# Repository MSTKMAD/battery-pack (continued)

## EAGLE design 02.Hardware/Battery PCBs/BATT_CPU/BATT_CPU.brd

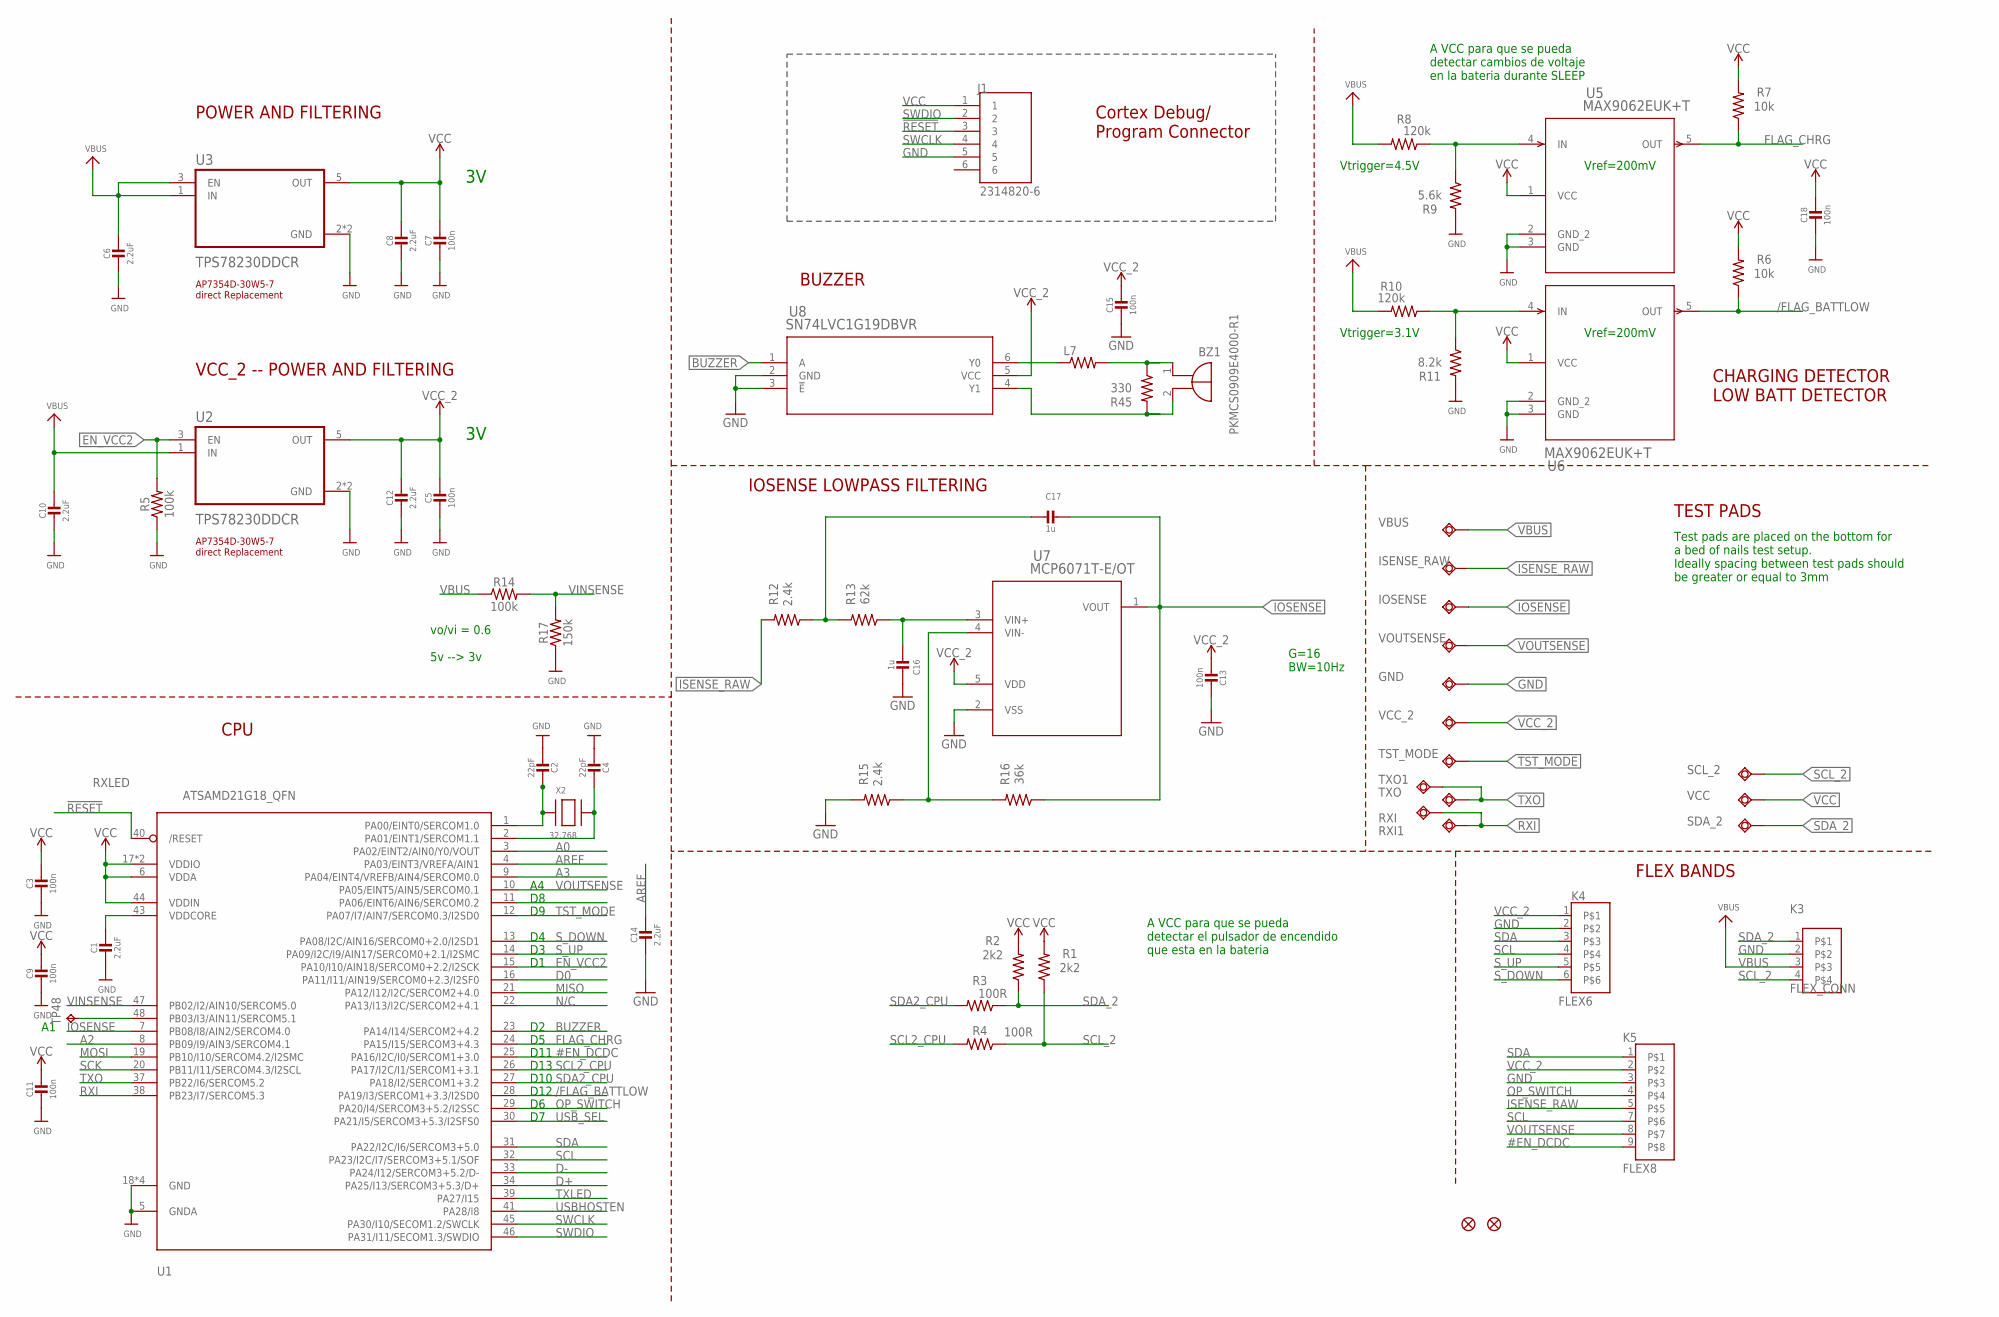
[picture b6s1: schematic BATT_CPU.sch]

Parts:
BZ1: PKMCS0909E4000-R1; PKMCS0909
C1, C14: 2.2uF; 0603-NO
C2, C4: 22pF; 0603-NO
C3, C5, C7, C9, C11, C13, C15, C18: 100n; 0603-NO
C6, C8, C10, C12: 2.2uF; 0805-NO
C16, C17: 1u; 0603-NO
GND: TESTPAD_TPSQB1,27; TESTPAD_B1,27
IOSENSE: TESTPAD_TPSQB1,27; TESTPAD_B1,27
ISENSE_RAW: TESTPAD_TPSQB1,27; TESTPAD_B1,27
J1: 2314820-6; TE_2314820-6
K3: FLEX_CONN; FLEX4
K4: FLEX6
K5: FLEX8
L7: MMZ2012Y202BT000; 0805
R1, R2: 2k2; 0603
R3, R4: 100R; 0603
R5, R14: 100k; 0603
R6, R7: 10k; 0603
R8, R10: 120k; 0603
R9: 5.6k; 0603
R11: 8.2k; 0603
R12, R15: 2.4k; 0603
R13: 62k; 0603
R16: 36k; 0603
R17: 150k; 0603
R45: 330; 0603
RXI, RXI1: TESTPAD_TPSQB1,27; TESTPAD_B1,27
SCL_2: TESTPAD_TPSQB1,27; TESTPAD_B1,27
SDA_2: TESTPAD_TPSQB1,27; TESTPAD_B1,27
TP48: TPTP08R; TP08R
TST_MODE: TESTPAD_TPSQB1,27; TESTPAD_B1,27
TXO, TXO1: TESTPAD_TPSQB1,27; TESTPAD_B1,27
U1: ATSAMD21G18_QFN; TQFN48_7MM
U2, U3: TPS78230DDCR; SOT95P280X110-5N
U5, U6: MAX9062EUK+T; 21-0057F_MXM
U7: MCP6071T-E/OT; SOT-23-5_MC_MCH
U8: SN74LVC1G19DBVR; DBV6
U$34, U$35: FIDUCIAL""; FIDUCIAL_1MM
VBUS: TESTPAD_TPSQB1,27; TESTPAD_B1,27
VCC: TESTPAD_TPSQB1,27; TESTPAD_B1,27
VCC_2: TESTPAD_TPSQB1,27; TESTPAD_B1,27
VOUTSENSE: TESTPAD_TPSQB1,27; TESTPAD_B1,27
X2: 32.768; XTAL3215

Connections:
!RESET: J1.3, U1.40 (/RESET)
#EN_DCDC: K5.9, U1.25 (PA16/I2C/I0/SERCOM1+3.0)
/FLAG_BATTLOW: R6.1, U1.28 (PA19/I3/SERCOM1+3.3/I2SD0), U6.5 (OUT)
A0: U1.3 (PA02/EINT2/AIN0/Y0/VOUT)
A2: U1.8 (PB09/I9/AIN3/SERCOM4.1)
A3: U1.9 (PA04/EINT4/VREFB/AIN4/SERCOM0.0)
AREF: C14.1, U1.4 (PA03/EINT3/VREFA/AIN1)
BUZZER: U1.23 (PA14/I14/SERCOM2+4.2), U8.1 (A)
D0: U1.16 (PA11/I11/AIN19/SERCOM0+2.3/I2SF0)
D+: U1.34 (PA25/I13/SERCOM3+5.3/D+)
D-: U1.33 (PA24/I12/SERCOM3+5.2/D-)
EN_VCC2: R5.2, U1.15 (PA10/I10/AIN18/SERCOM0+2.2/I2SCK), U2.3 (EN)
FLAG_CHRG: R7.1, U1.24 (PA15/I15/SERCOM3+4.3), U5.5 (OUT)
GND: C1.2, C2.2, C3.2, C4.2, C5.2, C6.2, C7.2, C8.2, C9.2, C10.2, C11.2, C12.2, C13.2, C14.2, C15.2, C16.2, C18.2, GND.TP, J1.5, K3.2, K4.2, K5.3, R5.1, R9.2, R11.2, R15.2, R17.1, U1.5 (GNDA), U1.18 (GND), U1.35 (GND), U1.42 (GND), U1.THERMAL (GND), U2.2 (GND), U2.4 (GND), U3.2 (GND), U3.4 (GND), U5.2 (GND_2), U5.3 (GND), U6.2 (GND_2), U6.3 (GND), U7.2 (VSS), U8.2 (GND), U8.3 (!E)
IOSENSE: C17.2, IOSENSE.TP, R16.1, U1.7 (PB08/I8/AIN2/SERCOM4.0), U7.1 (VOUT)
ISENSE_RAW: ISENSE_RAW.TP, K5.5, R12.2
MISO: U1.21 (PA12/I12/I2C/SERCOM2+4.0)
MOSI: U1.19 (PB10/I10/SERCOM4.2/I2SMC)
unnamed: R15.1, R16.2, U7.4 (VIN-)
unnamed: C2.1, U1.1 (PA00/EINT0/SERCOM1.0), X2.P$1
unnamed: C4.1, U1.2 (PA01/EINT1/SERCOM1.1), X2.P$2
unnamed: C17.1, R12.1, R13.2
unnamed: R10.1, R11.1, U6.4 (IN)
unnamed: R8.1, R9.1, U5.4 (IN)
unnamed: C16.1, R13.1, U7.3 (VIN+)
unnamed: TP48.TP, U1.48 (PB03/I3/AIN11/SERCOM5.1)
unnamed: L7.1, U8.6 (Y0)
unnamed: BZ1.1 (+), L7.2, R45.1
unnamed: BZ1.2 (-), R45.2, U8.4 (Y1)
OP_SWITCH: K5.4, U1.29 (PA20/I4/SERCOM3+5.2/I2SSC)
RXI: RXI.TP, RXI1.TP, U1.38 (PB23/I7/SERCOM5.3)
SCK: U1.20 (PB11/I11/SERCOM4.3/I2SCL)
SCL: K4.4, K5.7, U1.32 (PA23/I2C/I7/SERCOM3+5.1/SOF)
SCL2_CPU: R4.2, U1.26 (PA17/I2C/I1/SERCOM1+3.1)
SCL_2: K3.4, R1.1, R4.1, SCL_2.TP
SDA: K4.3, K5.1, U1.31 (PA22/I2C/I6/SERCOM3+5.0)
SDA2_CPU: R3.2, U1.27 (PA18/I2/SERCOM1+3.2)
SDA_2: K3.1, R2.1, R3.1, SDA_2.TP
SWCLK: J1.4, U1.45 (PA30/I10/SECOM1.2/SWCLK)
SWDIO: J1.2, U1.46 (PA31/I11/SECOM1.3/SWDIO)
S_DOWN: K4.6, U1.13 (PA08/I2C/AIN16/SERCOM0+2.0/I2SD1)
S_UP: K4.5, U1.14 (PA09/I2C/I9/AIN17/SERCOM0+2.1/I2SMC)
TST_MODE: TST_MODE.TP, U1.12 (PA07/I7/AIN7/SERCOM0.3/I2SD0)
TXO: TXO.TP, TXO1.TP, U1.37 (PB22/I6/SERCOM5.2)
USB_SEL: U1.30 (PA21/I5/SERCOM3+5.3/I2SFS0)
VBUS: C6.1, C10.1, K3.3, R8.2, R10.2, R14.1, U2.1 (IN), U3.1 (IN), U3.3 (EN), VBUS.TP
VCC: C3.1, C7.1, C8.1, C9.1, C11.1, C18.1, J1.1, R1.2, R2.2, R6.2, R7.2, U1.6 (VDDA), U1.17 (VDDIO), U1.36 (VDDIO), U1.44 (VDDIN), U3.5 (OUT), U5.1 (VCC), U6.1 (VCC), VCC.TP
VCC_2: C5.1, C12.1, C13.1, C15.1, K4.1, K5.2, U2.5 (OUT), U7.5 (VDD), U8.5 (VCC), VCC_2.TP
VDDCORE: C1.1, U1.43 (VDDCORE)
VINSENSE: R14.2, R17.2, U1.47 (PB02/I2/AIN10/SERCOM5.0)
VOUTSENSE: K5.8, U1.10 (PA05/EINT5/AIN5/SERCOM0.1), VOUTSENSE.TP

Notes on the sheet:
POWER AND FILTERING
N/C
TXLED
USBHOSTEN
RXLED
Cortex Debug/ Program Connector
BUZZER
AP7354D-30W5-7 direct Replacement
VCC_2 -- POWER AND FILTERING
A VCC para que se pueda detectar el pulsador de encendido que esta en la bateria
D10
A VCC para que se pueda detectar cambios de voltaje en la bateria durante SLEEP
G=16 BW=10Hz
IOSENSE LOWPASS FILTERING
FLEX BANDS
CHARGING DETECTOR LOW BATT DETECTOR
CPU
Vref=200mV
Vtrigger=4.5V
Vtrigger=3.1V
D13
D11
D12
TEST PADS
Test pads are placed on the bottom for a bed of nails test setup. Ideally spacing between test pads should be greater or equal to 3mm
vo/vi = 0.6 5v --> 3v

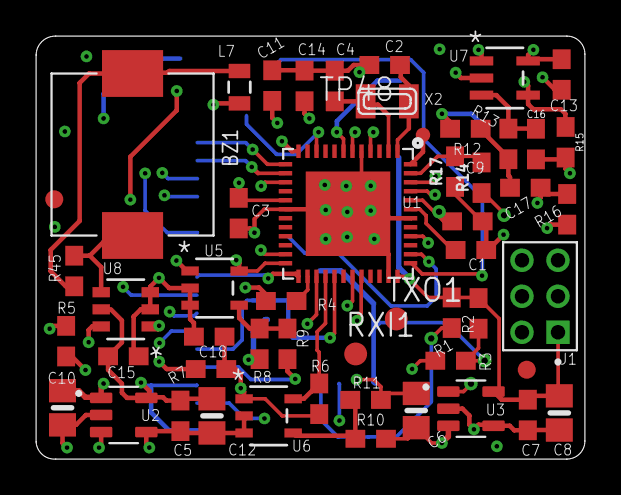
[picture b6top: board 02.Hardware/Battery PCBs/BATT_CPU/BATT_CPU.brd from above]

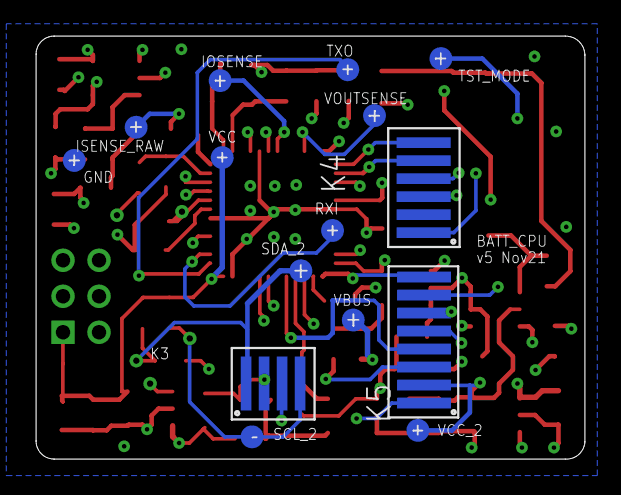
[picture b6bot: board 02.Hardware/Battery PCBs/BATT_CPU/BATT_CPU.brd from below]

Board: 4 copper layers, 30.5 x 23.5 mm, 67 parts (15 on the bottom side), 41 nets.

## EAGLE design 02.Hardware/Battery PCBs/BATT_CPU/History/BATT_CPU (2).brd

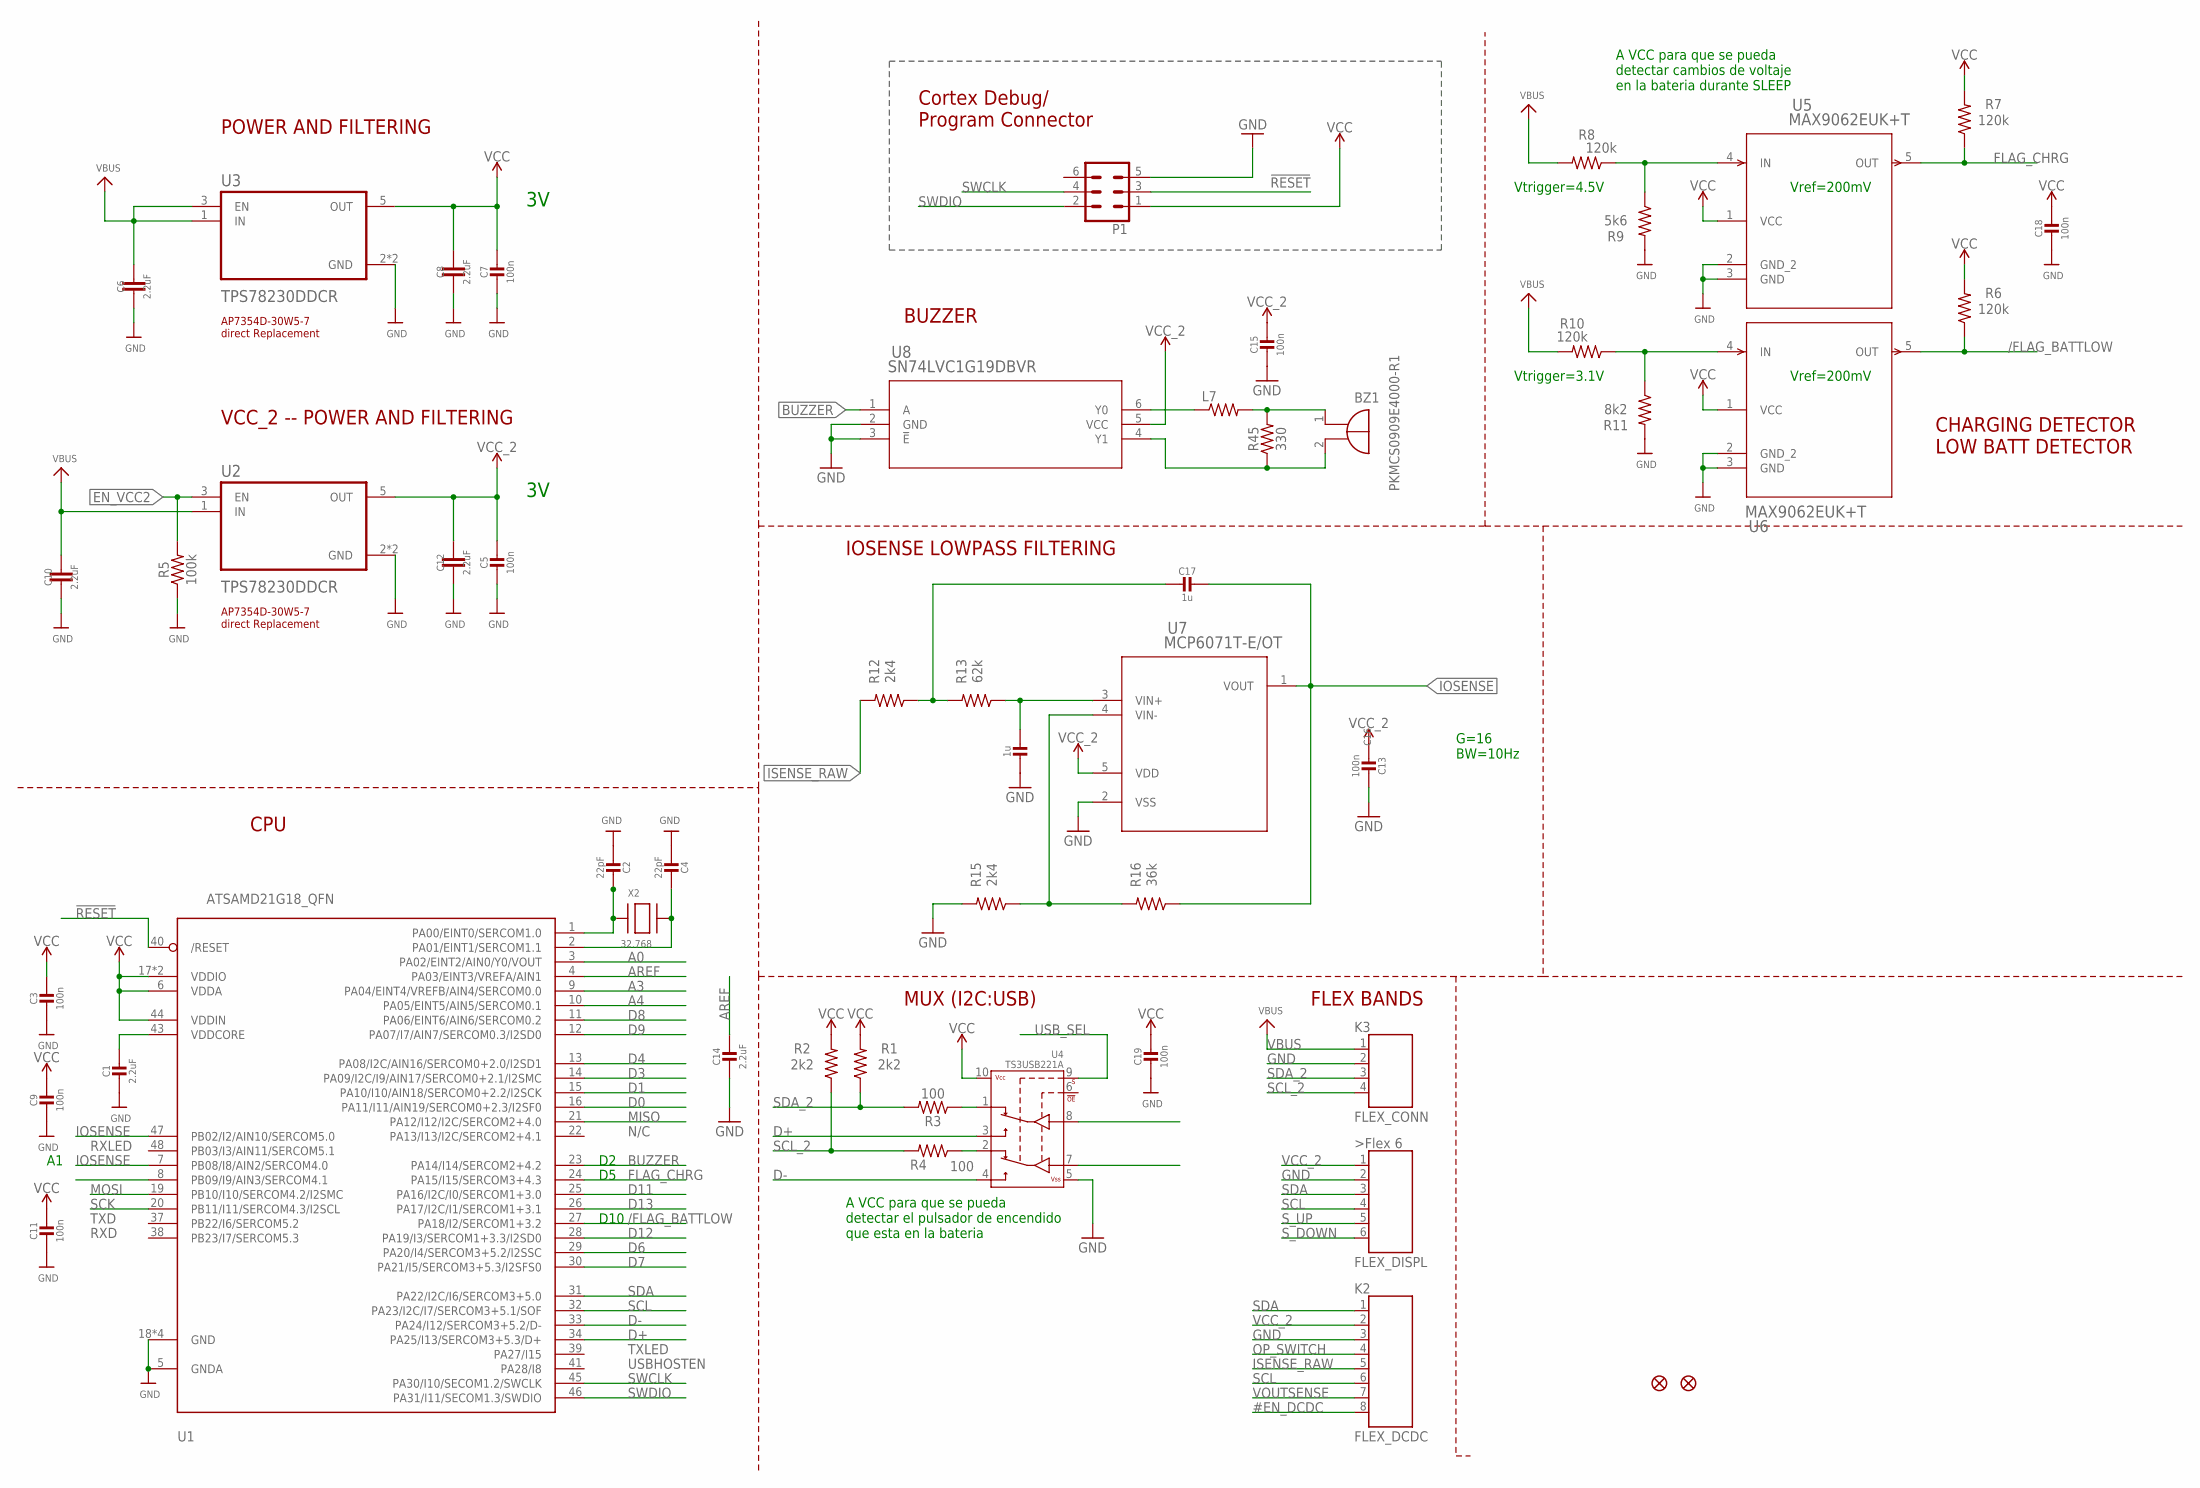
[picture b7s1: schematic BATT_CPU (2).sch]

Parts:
BZ1: PKMCS0909E4000-R1; PKMCS0909
C1, C14: 2.2uF; 0603-NO
C2, C4: 22pF; 0603-NO
C3, C5, C7, C9, C11, C13, C15, C18, C19: 100n; 0603-NO
C6, C8, C10, C12: 2.2uF; 0603
C16, C17: 1u; 0603-NO
K1: FLEX_DISPL; FLEX6
K2: FLEX_DCDC; FLEX8
K3: FLEX_CONN; FLEX4
L7: MMZ2012Y202BT000; 0805
P1: CONN03X2-PROGRAM-POGO-SWD-1.27; 2X3-PROGRAM-POGO-SWD-1.27
R1, R2: 2k2; 0402
R3, R4: 100; 0402
R5: 100k; 0402
R6, R7, R8, R10: 120k; 0402
R9: 5k6; 0402
R11: 8k2; 0402
R12, R15: 2k4; 0402
R13: 62k; 0402
R16: 36k; 0402
R45: 330; 0402
U1: ATSAMD21G18_QFN; TQFN48_7MM
U2, U3: TPS78230DDCR; SOT95P280X110-5N
U4: TS3USB221A; QFN-10-RSE
U5, U6: MAX9062EUK+T; 21-0057F_MXM
U7: MCP6071T-E/OT; SOT-23-5_MC_MCH
U8: SN74LVC1G19DBVR; DBV6
U$34, U$35: FIDUCIAL""; FIDUCIAL_1MM
X2: 32.768; XTAL3215

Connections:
!RESET: P1.3, U1.40 (/RESET)
#EN_DCDC: K2.8
/FLAG_BATTLOW: R6.1, U1.27 (PA18/I2/SERCOM1+3.2), U6.5 (OUT)
A0: U1.3 (PA02/EINT2/AIN0/Y0/VOUT)
A3: U1.9 (PA04/EINT4/VREFB/AIN4/SERCOM0.0)
A4: U1.10 (PA05/EINT5/AIN5/SERCOM0.1)
AREF: C14.1, U1.4 (PA03/EINT3/VREFA/AIN1)
BUZZER: U1.23 (PA14/I14/SERCOM2+4.2), U8.1 (A)
D0: U1.16 (PA11/I11/AIN19/SERCOM0+2.3/I2SF0)
D1: U1.15 (PA10/I10/AIN18/SERCOM0+2.2/I2SCK)
D3: U1.14 (PA09/I2C/I9/AIN17/SERCOM0+2.1/I2SMC)
D4: U1.13 (PA08/I2C/AIN16/SERCOM0+2.0/I2SD1)
D6: U1.29 (PA20/I4/SERCOM3+5.2/I2SSC)
D7: U1.30 (PA21/I5/SERCOM3+5.3/I2SFS0)
D8: U1.11 (PA06/EINT6/AIN6/SERCOM0.2)
D9: U1.12 (PA07/I7/AIN7/SERCOM0.3/I2SD0)
D11: U1.25 (PA16/I2C/I0/SERCOM1+3.0)
D12: U1.28 (PA19/I3/SERCOM1+3.3/I2SD0)
D13: U1.26 (PA17/I2C/I1/SERCOM1+3.1)
D+: U1.34 (PA25/I13/SERCOM3+5.3/D+), U4.3 (2D+)
D-: U1.33 (PA24/I12/SERCOM3+5.2/D-), U4.4 (2D-)
EN_VCC2: R5.2, U2.3 (EN)
FLAG_CHRG: R7.1, U1.24 (PA15/I15/SERCOM3+4.3), U5.5 (OUT)
GND: C1.2, C2.2, C3.2, C4.2, C5.2, C6.2, C7.2, C8.2, C9.2, C10.2, C11.2, C12.2, C13.2, C14.2, C15.2, C16.2, C18.2, C19.2, K1.2, K2.3, K3.2, P1.5, R5.1, R9.2, R11.2, R15.2, U1.5 (GNDA), U1.18 (GND), U1.35 (GND), U1.42 (GND), U1.THERMAL (GND), U2.2 (GND), U2.4 (GND), U3.2 (GND), U3.4 (GND), U4.5 (VSS), U5.2 (GND_2), U5.3 (GND), U6.2 (GND_2), U6.3 (GND), U7.2 (VSS), U8.2 (GND), U8.3 (!E)
IOSENSE: C17.2, R16.1, U1.7 (PB08/I8/AIN2/SERCOM4.0), U1.47 (PB02/I2/AIN10/SERCOM5.0), U7.1 (VOUT)
ISENSE_RAW: K2.5, R12.2
MISO: U1.21 (PA12/I12/I2C/SERCOM2+4.0)
MOSI: U1.19 (PB10/I10/SERCOM4.2/I2SMC)
unnamed: R15.1, R16.2, U7.4 (VIN-)
unnamed: R3.1, U4.1 (1D+)
unnamed: R4.1, U4.2 (1D-)
unnamed: C2.1, U1.1 (PA00/EINT0/SERCOM1.0), X2.P$1
unnamed: C4.1, U1.2 (PA01/EINT1/SERCOM1.1), X2.P$2
unnamed: C17.1, R12.1, R13.2
unnamed: R10.1, R11.1, U6.4 (IN)
unnamed: R8.1, R9.1, U5.4 (IN)
unnamed: C16.1, R13.1, U7.3 (VIN+)
unnamed: L7.1, U8.6 (Y0)
unnamed: BZ1.1 (+), L7.2, R45.2
unnamed: BZ1.2 (-), R45.1, U8.4 (Y1)
OP_SWITCH: K2.4
SCK: U1.20 (PB11/I11/SERCOM4.3/I2SCL)
SCL: K1.4, K2.6, U1.32 (PA23/I2C/I7/SERCOM3+5.1/SOF)
SCL_2: K3.4, R2.1, R4.2
SDA: K1.3, K2.1, U1.31 (PA22/I2C/I6/SERCOM3+5.0)
SDA_2: K3.3, R1.1, R3.2
SWCLK: P1.4, U1.45 (PA30/I10/SECOM1.2/SWCLK)
SWDIO: P1.2, U1.46 (PA31/I11/SECOM1.3/SWDIO)
S_DOWN: K1.6
S_UP: K1.5
USB_SEL: U4.9 (S)
VBUS: C6.1, C10.1, K3.1, R8.2, R10.2, U2.1 (IN), U3.1 (IN), U3.3 (EN)
VCC: C3.1, C7.1, C8.1, C9.1, C11.1, C18.1, C19.1, P1.1, R1.2, R2.2, R6.2, R7.2, U1.6 (VDDA), U1.17 (VDDIO), U1.36 (VDDIO), U1.44 (VDDIN), U3.5 (OUT), U4.10 (VCC), U5.1 (VCC), U6.1 (VCC)
VCC_2: C5.1, C12.1, C13.1, C15.1, K1.1, K2.2, U2.5 (OUT), U7.5 (VDD), U8.5 (VCC)
VDDCORE: C1.1, U1.43 (VDDCORE)
VOUTSENSE: K2.7

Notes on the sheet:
POWER AND FILTERING
N/C
TXLED
USBHOSTEN
RXLED
TXD
RXD
Cortex Debug/ Program Connector
BUZZER
AP7354D-30W5-7 direct Replacement
VCC_2 -- POWER AND FILTERING
A VCC para que se pueda detectar el pulsador de encendido que esta en la bateria
D10
A VCC para que se pueda detectar cambios de voltaje en la bateria durante SLEEP
G=16 BW=10Hz
IOSENSE LOWPASS FILTERING
FLEX BANDS
MUX (I2C:USB)
CHARGING DETECTOR LOW BATT DETECTOR
CPU
Vref=200mV
Vtrigger=4.5V
Vtrigger=3.1V

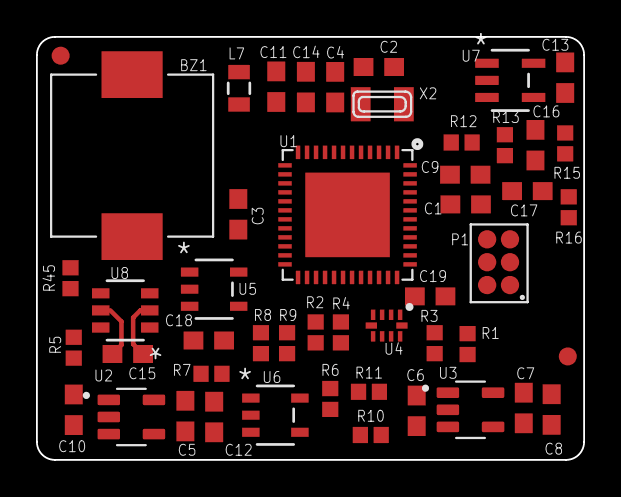
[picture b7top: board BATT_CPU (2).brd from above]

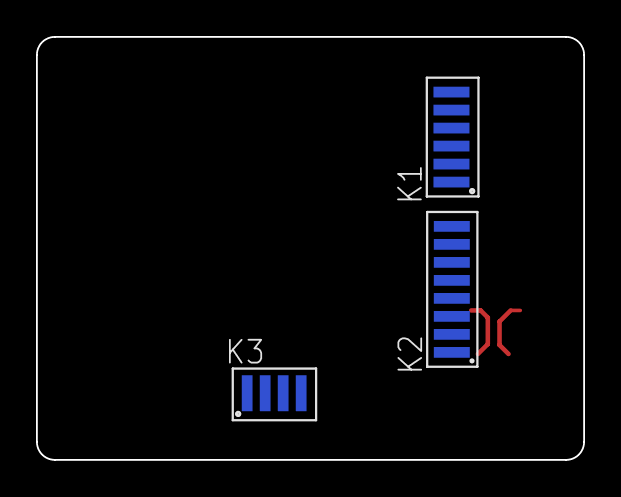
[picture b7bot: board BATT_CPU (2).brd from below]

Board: 2 copper layers, 30.4 x 23.5 mm, 52 parts (3 on the bottom side), 33 nets.
